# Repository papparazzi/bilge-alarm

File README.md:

# Bilge alarm - M/Y Lada Panas (NMEA 2000 bilge monitor)

Custom 100 x 100 mm, 2-layer PCB for the M/Y Lada Panas (Princess 366, Singapore). It sits behind the helm MFD, watches three pump-sense inputs and a high-water float, drives a light and a buzzer, and reports on an isolated NMEA 2000 (CAN) connection. **Status (11 November 2026): the Rev C.5 boards are built and board 1 works as designed on the bench. Power, all four inputs, the sensor, Wi-Fi and the web page are tested, and the alarm firmware (1.0.0-rc1) runs on it. Still to test, on the boat: the light and buzzer outputs with real loads, and NMEA 2000 on a live network.** Details under [Test status and known risks](#test-status-and-known-risks).

Board 1 running the alarm firmware from 12 V, in the printed enclosure base.

## 3D-printed enclosure

A two-part case (base + removable cover, M3 heat-set inserts, cable strain relief, tie-down lugs) designed to sit behind the helm display. The picture shows the base with the real board (KiCad 10 STEP export with silkscreen) and the ESP32 dev board fitted, cover off. Print files, the parametric Fusion script and rebuild instructions are in [`case/`](case/README.md). **Printed in November 2026; the photo at the top shows the real board in the printed base.**

## Gallery
**The real thing** (November 2026): the dev-board sockets with their pin labels, and the ESP32-S3 dev board that plugs into them.

**The board** (Rev C.5, KiCad 10 ray-traced renders of the real design file):

**The enclosure** (Fusion renders; the board and the ESP32 dev board are the real models/photo):

## What it does
- **Brain:** ESP32-S3-DevKitC-1 clone (N8R2/N16R8) on two 1x22 sockets. The ESP32 module is not assembled by JLCPCB's Economic service, so the dev board is bought separately and plugged in.
- **Power:** 12 V boat battery in, reverse-polarity P-FET, 24.4 V TVS, 2 A PPTC, AP63205 5 V buck feeding the dev-board 5V pin through a Schottky (the dev board makes 3.3 V).
- **Inputs:** three pump-sense inputs and a high-water float (100k/27k dividers, ADC), supply-voltage sense, MUTE button.
- **Outputs:** light and buzzer switched on the **positive** (high-side AO3401A P-FETs, driven by AO3400A), flyback diodes, and a **hard-wired bypass** so the float turns both outputs on even if the ESP32 is dead.
- **NMEA 2000:** CA-IS3050G isolated CAN transceiver (5 kVrms), 8.85 mm copper gap, bus-side L78L05 supply.
- **Sensor:** TE MS5637-02BA03 pressure + temperature on I2C 0x76 (compartment temperature; no humidity).
- **Indicators:** two red LEDs (status, alarm), widely spaced.
- **Extras:** all unused dev-board pins plus 3V3 / 5V / GND and SDA/SCL are broken out on numbered pad rows for solder-on sensors; four M3 corner holes for a 3D-printed case; the Lada Panas logo (32 mm) on the silkscreen.

## Firmware
The alarm firmware is in [`firmware/bilge_alarm`](firmware/bilge_alarm/README.md) (version 1.0.0-rc1, Arduino core for ESP32, built with arduino-cli or the Arduino IDE). It runs on board 1.

- **Alarms:** high water (float), pump running too long, pump starting too often, supply voltage low. Limits are set on the web page.
- **Counts since power-on:** how often and how long each input was on, how often each alarm was raised, and a log of the last 80 events. They survive a restart and a firmware update.
- **Web page** on the boat's Wi-Fi, with every reading the board has. If the board cannot join its saved network it opens its own setup hotspot, where a network can be chosen. Firmware updates are uploaded from the same page.
- **NMEA 2000:** pump and float states, supply voltage, pressure, temperature, and alarms as alert messages for a chartplotter (written for a Raymarine Axiom). Not yet tried on a network.
- **Bluetooth:** advertises as a RuuviTag temperature and pressure sensor for a Victron Cerbo GX. Not yet tried against a Cerbo.

The page as served by board 1 on the bench, in setup-hotspot mode. Nothing is connected to the NMEA 2000 port, so that card reads "no other device answers".

## Repository layout
| Folder | Contents |
|---|---|
| `docs/` | Design decisions, dev-board pin map, holistic review, JLCPCB quotes and sensor comparison, bring-up checklist, DRC and verification output |
| `firmware/` | `bilge_alarm/` is the alarm firmware, `bench_test/` the sketch used to check a new board (arduino-cli, ESP32 Arduino core 3.x). Build, flash and bench instructions are in `firmware/README.md`; the research behind the NMEA 2000, Signal K and Victron choices is `docs/FIRMWARE_ARCHITECTURE.md` |
| `kicad/` | KiCad 10 board: `bilge_n2k_revC.kicad_pcb` (placed, unrouted) and `bilge_n2k_revC_routed.kicad_pcb` (final) |
| `gen/` | Python generators: `design_revC.py` is the single source of the netlist and BOM; `build_pcb.py` places the board; `route_clean.sh` autoroutes (Freerouting) until DRC is clean; `verify_board.py`, `fix_silk.py`, `fix_refs.py`, `export_fab.sh`, `make_quote_files.py`, `make_logo.py` do the rest. `fp/` holds the custom MS5637 footprint |
| `case/` | 3D-printed enclosure: STL/STEP in `print/`, parametric Fusion script in `BilgeCase/`, KiCad STEP exports and ESP32 texture in `ref/`, renders, build notes in `case/README.md` |
| `quote_jlcpcb/` | Files uploaded to JLCPCB: Gerbers + drill zip, BOM, CPL (Economic assembly, top side) |
| `mfg/` | Assembly and copper previews, netlist |
| `logo/` | Source logo and the silkscreen preview |
| `datasheets/` | Datasheets, dev-board dimension drawings and the clone photos used for the footprint; see `SOURCES.md` |
| `review/` | Self-contained zip for an independent reviewer |

## Rebuilding
Needs KiCad 10, Java 25 and Freerouting 2.5 (paths are set at the top of `gen/route.sh`), Python 3 with OpenCV for the logo.
```
python3 gen/design_revC.py            # netlist, BOM, cost
kicad-python gen/build_pcb.py         # place the board (KiCad's bundled Python)
gen/route_clean.sh                    # route until DRC is clean
gen/verify_board.py, gen/fix_silk.py, gen/fix_refs.py, gen/export_fab.sh, gen/make_quote_files.py
```
`gen/make_all.sh` shows the original sequence. Scripts assume this folder layout.

## Ordering (JLCPCB)
Economic assembly, top side, 5 boards: **US$92.12** at the last quote (PCB $4.00, assembly $88.12 including an $18.54 extended-component fee), 26 BOM lines. The MS5637 is flagged "difficult to process" by JLCPCB and must be ticked by hand; they may refuse or surcharge it (fallback: leave it unpopulated and hand-solder). Details in `docs/QUOTES_revC.md`.

## Test status and known risks
The board works as designed in everything tested so far. All testing has been on the bench with board 1; nothing has run on the boat yet. Full results are in `docs/BENCH_RESULTS.md`.

| Area | State |
|---|---|
| Power from 12 V (reverse-polarity FET, 5 V buck) | Tested, works |
| Dev board on the sockets: pin order, power pins, flashing over USB | Tested, works |
| Inputs IN1 to IN4 with 12 V applied | Tested, work |
| Supply voltage reading | Tested, works (read 13.15 V on the bench supply) |
| Pressure and temperature sensor (MS5637, custom footprint) | Tested, works |
| Status LED, MUTE button | Tested, work |
| Wi-Fi, setup hotspot, web page, firmware update over Wi-Fi | Tested, work |
| Alarm logic, counters, event log | Tested with the low-voltage alarm and real 12 V on two inputs |
| Light and buzzer outputs | **Pending.** The pins switch, but no load has been connected |
| Hard-wired float bypass, alarm LED | **Pending** |
| NMEA 2000 | **Pending field test.** The firmware sends with no network attached and never holds anything up; the port has not been on a real network |
| Bluetooth to the Cerbo GX | **Pending.** Advertising runs; not tried against a Cerbo |

Risks closed by the bench test:
- The dev-board clone's pin order and its 3V3 / 5V / GND pins were taken from seller photos and a drawing. They are right: the board runs on the sockets and every tested function is on the expected pin.
- The custom MS5637 footprint and JLCPCB's manual-review risk: the sensor was assembled, answers and passes its calibration check.

Risks still open:
- **Outputs.** The high-side light and buzzer stage has never driven a real load, and the hard-wired bypass (float switches both outputs without the ESP32) has not been tried.
- **NMEA 2000.** Untested on a network. The alarm messages (PGN 126983 / 126985) are built by hand and checked only against the canboat database; a Raymarine Axiom needs LightHouse 4 v4.8.164 or later to show them. The heat of the L78L05 on a 14 to 16 V bus has not been measured.
- **Supply reading.** Single readings jump by up to 1 V with Wi-Fi on; the firmware filters them. The reading may stop rising at about 14.1 V, to be confirmed with an adjustable supply.
- **IN1 and IN2 share their converter (ADC2) with Wi-Fi.** No failed reading so far (about 2.5 million each over a nine-hour run, in hotspot mode and on a normal network); the firmware counts failures and shows them. A next board revision should move them to ADC1.
- **One unexplained restart.** The board once reported a brownout as its last restart cause on the bench. It may only have been the moment 12 V was switched on.
- **USB and 12 V connected at the same time** has not been tested.
- **By design:** while the float is up, the hardware holds light and buzzer on and MUTE cannot silence them.
- **Network access is basic.** Anyone on the same network can read the page; changes ask for a login only once an admin password is set.
- The autorouted layout has not been reviewed by a human (buck loop, CAN pair), and nothing has been measured for emissions.
- Only board 1 has been powered, and only on the bench: no heat, vibration or damp-air exposure yet.

Earlier design notes: `docs/HOLISTIC_REVIEW_revC3.md` and `docs/BRINGUP_CHECKLIST.md`.

## Revision history (short)
Rev C.1-C.3: JLCPCB-only, high-side outputs, MS5637, 100 x 100 mm, I/O on one edge. Rev C.4: re-layout for the clone's real 25.40 mm row spacing. Rev C.5: external-review fixes (22 uF buck output caps, 22k gate pull-ups so |Vgs| stays under 12 V, 470 ohm LED resistors, 2 A PPTC), full silkscreen cleanup, Lada Panas logo.

Datasheets and vendor drawings in `datasheets/` belong to their manufacturers and are included for reference only.

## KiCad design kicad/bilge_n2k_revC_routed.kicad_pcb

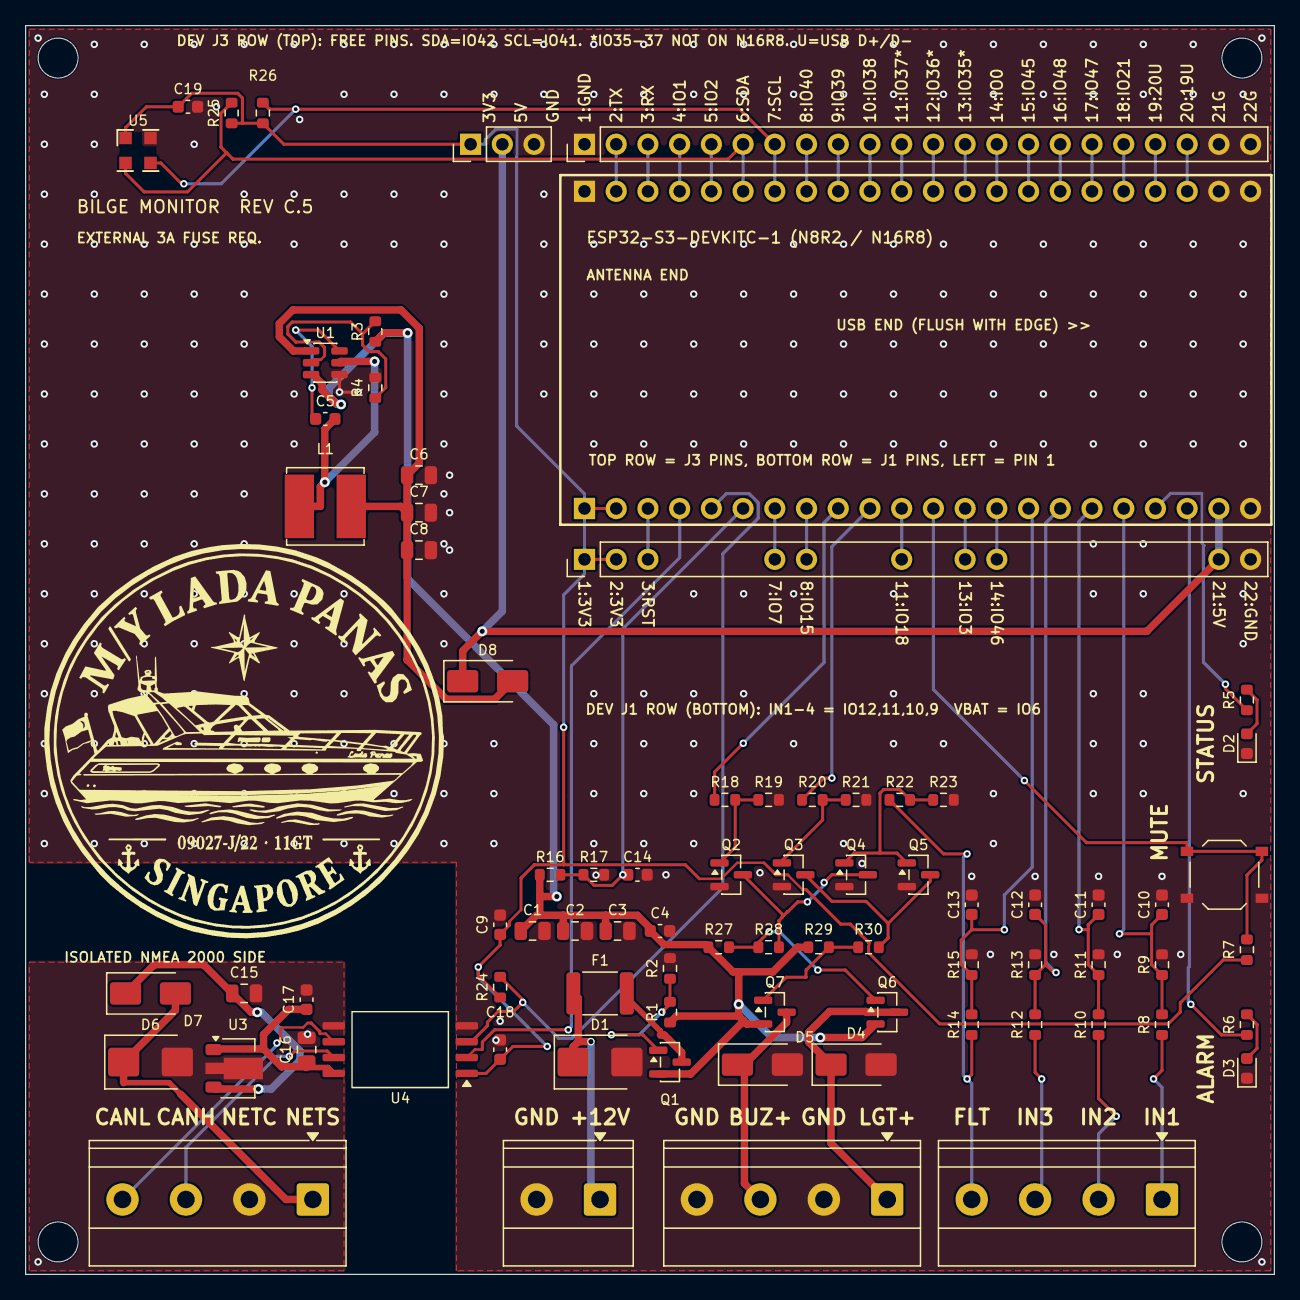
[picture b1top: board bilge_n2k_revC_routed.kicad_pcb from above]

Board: 2 copper layers, 100.0 x 100.0 mm, 84 parts (0 on the bottom side), 69 nets.

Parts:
BR1, BR2: M3; PinHeader_1x22_P2.54mm_Vertical
C1, C2, C3, C15, C16: CL21A106KAYNNNE; C_0805_2012Metric
C4, C5, C9, C10, C11, C12, C13, C14, C17, C18, C19: CC0603KRX7R9BB104; C_0603_1608Metric
C6, C7, C8: CL21A226MAQNNNE; C_0805_2012Metric
D1, D6: SMBJ15CA; D_SMB
D2, D3: KT-0603R; LED_0603_1608Metric
D4, D5, D7, D8: SS14; D_SMA
F1: SMD1812-200-24; Fuse_1812_4532Metric
H1, H2, H3, H4: M3; MountingHole_3.2mm_M3
HDR1, HDR2: HC-PM254-8.5H-1x22PZ; PinSocket_1x22_P2.54mm_Vertical
J1: DB127S-5.08-2P-GN-S; TerminalBlock_Phoenix_MKDS-1,5-2-5.08_1x02_P5.08mm_Horizont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
J2, J3, J4: DB127S-5.08-4P-GN-S; TerminalBlock_Phoenix_MKDS-1,5-4-5.08_1x04_P5.08mm_Horizont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
L1: SRN6045TA-4R7M; L_Bourns_SRN6045TA
PW1: M3; PinHeader_1x03_P2.54mm_Vertical
Q1, Q6, Q7: AO3401A; SOT-23
Q2, Q3, Q4, Q5: AO3400A; SOT-23
R1, R4, R23, R28, R30: 0603WAF4702T5E; R_0603_1608Metric
R2, R3, R8, R10, R12, R14, R16, R19, R21, R22: 0603WAF1003T5E; R_0603_1608Metric
R5, R6: 0603WAF4700T5E; R_0603_1608Metric
R7, R24: 0603WAF1002T5E; R_0603_1608Metric
R9, R11, R13, R15, R17: 0603WAF2702T5E; R_0603_1608Metric
R18, R20: 0603WAF1001T5E; R_0603_1608Metric
R25, R26: 0603WAF5101T5E; R_0603_1608Metric
R27, R29: 0603WAF2202T5E; R_0603_1608Metric
SW3: TS-1187A-B-A-B; SW_Push_1P1T_XKB_TS-1187A
U1: AP63205WU-7; TSOT-23-6
U3: L78L05ABUTR; SOT-89-3
U4: CA-IS3050G; SOIC-8_7.5x5.85mm_P1.27mm
U5: MS563702BA03-50; MS5637-02BA03_QFN-4_3x3mm

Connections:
+3V3: BR1.1, BR1.2, C9.1, C18.1, C19.1, HDR1.1, HDR1.2, PW1.1, R7.1, R24.1, R25.1, R26.1, U4.1, U5.1
+5V: C6.1, C7.1, C8.1, D8.2, L1.2, U1.1
+5V_ISO: C16.1, C17.1, U3.1, U4.8
BST: C5.1, U1.6
BTN_MUTE: HDR1.12, R7.2, SW3.1
BUZZ_CTL: HDR1.10, R20.1
BUZZ_OUT: D5.1, J3.3, Q7.3
B_G: Q3.1, R20.2, R21.1
B_PD: Q3.3, Q5.3, R30.2
B_PG: Q7.1, R29.2, R30.1
CANH_J: J4.3, U4.7
CANL_J: J4.4, U4.6
CAN_RX: HDR1.4, U4.2
CAN_TX: HDR1.5, R24.2, U4.3
DEV_5V: BR1.21, D8.1, HDR1.21, PW1.2
EN_BUCK: R3.2, R4.1, U1.2
GND: BR1.22, BR2.1, BR2.21, BR2.22, C1.2, C2.2, C3.2, C4.2, C6.2, C7.2, C8.2, C9.2, C10.2, C11.2, C12.2, C13.2, C14.2, C18.2, C19.2, D1.2, D2.1, D3.1, D4.2, D5.2, HDR1.22, HDR2.1, HDR2.21, HDR2.22, J1.2, J3.2, J3.4, PW1.3, Q2.2, Q3.2, Q4.2, Q5.2, R2.2, R4.2, R9.2, R11.2, R13.2, R15.2, R17.2, R19.2, R21.2, R23.2, SW3.2, U1.4, U4.4, U5.4
HW_G: Q4.1, Q5.1, R22.2, R23.1
I2C_SCL: BR2.7, HDR2.7, R26.2, U5.3
I2C_SDA: BR2.6, HDR2.6, R25.2, U5.2
IN1_A: C10.1, HDR1.18, R8.2, R9.1
IN1_RAW: J2.1, R8.1
IN2_A: C11.1, HDR1.17, R10.2, R11.1
IN2_RAW: J2.2, R10.1
IN3_A: C12.1, HDR1.16, R12.2, R13.1
IN3_RAW: J2.3, R12.1
IN4_A: C13.1, HDR1.15, R14.2, R15.1
IN4_RAW: J2.4, R14.1, R22.1
J1_P3: BR1.3, HDR1.3
J1_P7: BR1.7, HDR1.7
J1_P8: BR1.8, HDR1.8
J1_P11: BR1.11, HDR1.11
J1_P13: BR1.13, HDR1.13
J1_P14: BR1.14, HDR1.14
J3_P2: BR2.2, HDR2.2
J3_P3: BR2.3, HDR2.3
J3_P4: BR2.4, HDR2.4
J3_P5: BR2.5, HDR2.5
J3_P8: BR2.8, HDR2.8
J3_P9: BR2.9, HDR2.9
J3_P10: BR2.10, HDR2.10
J3_P11: BR2.11, HDR2.11
J3_P12: BR2.12, HDR2.12
J3_P13: BR2.13, HDR2.13
J3_P14: BR2.14, HDR2.14
J3_P15: BR2.15, HDR2.15
J3_P16: BR2.16, HDR2.16
J3_P17: BR2.17, HDR2.17
J3_P18: BR2.18, HDR2.18
J3_P19: BR2.19, HDR2.19
J3_P20: BR2.20, HDR2.20
LED_ALM: HDR1.20, R6.1
LED_ALM_A: D3.2, R6.2
LED_STAT: HDR1.19, R5.1
LED_STAT_A: D2.2, R5.2
LIGHT_CTL: HDR1.9, R18.1
LIGHT_OUT: D4.1, J3.1, Q6.3
L_G: Q2.1, R18.2, R19.1
L_PD: Q2.3, Q4.3, R28.2
L_PG: Q6.1, R27.2, R28.1
NET_C: C15.2, C16.2, C17.2, D6.2, J4.2, U3.2, U4.5
NET_S: D6.1, D7.2, J4.1
NET_SP: C15.1, D7.1, U3.3
Q1_G: Q1.1, R1.2, R2.1
SW: C5.2, L1.1, U1.5
VBAT_IN: D1.1, F1.1, J1.1
VFUSED: F1.2, Q1.3
VIN: C1.1, C2.1, C3.1, C4.1, Q1.2, Q6.2, Q7.2, R1.1, R3.1, R16.1, R27.1, R29.1, U1.3
VSENSE_A: C14.1, HDR1.6, R16.2, R17.1

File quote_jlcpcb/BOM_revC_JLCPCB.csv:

Comment,Designator,Footprint,LCSC Part #
10 uF 25 V X5R 0805,"C1,C2,C3,C15,C16",C0805,C15850
100 nF 50 V X7R 0603 (JLCPCB Basic),"C4,C5,C9,C10,C11,C12,C13,C14,C17,C18,C19",C0603,C14663
22 uF 25 V X5R 0805 (JLCPCB Basic; buck COUT per AP63205 DS41326),"C6,C7,C8",C0805,C45783
"TVS 600 W bidirectional, VRWM 15 V, VBR 16.7-18.5 V, VC 24.4 V","D1,D6",DO-214AA (SMB),C19077570
LED red 0603,"D2,D3",LED0603,C2286
Schottky 40 V 1 A,"D4,D5,D7,D8",DO-214AC (SMA),C2480
"PPTC 2 A hold, 4 A trip, 24 V",F1,1812,C46641174
"1x22 female header 2.54 mm, 8.5 mm tall (dev-board socket)","HDR1,HDR2",THT 2.54 mm 1x22,C41376161
"Screw terminal 5.08 mm, 2 pos, side entry",J1,THT 5.08 mm,C2997519
"Screw terminal 5.08 mm, 4 pos, side entry","J2,J3,J4",THT 5.08 mm,C2997521
"4.7 uH 20 %, shielded, 6x6 mm (4.7 uH = AP63205 datasheet Table 3 for 5 V out)",L1,SMD 6x6 mm,C2044594
"P-MOSFET -30 V -4 A, VGS +-12 V","Q1,Q6,Q7",SOT-23,C15127
"N-MOSFET 30 V 5.7 A, VGS +-12 V, logic level","Q2,Q3,Q4,Q5",SOT-23,C20917
47 k 1 % 0603,"R1,R4,R23,R28,R30",R0603,C25819
100 k 1 % 0603,"R2,R3,R8,R10,R12,R14,R16,R19,R21,R22",R0603,C25803
470 ohm 1 % 0603,"R5,R6",R0603,C23179
10 k 1 % 0603,"R7,R24",R0603,C25804
27 k 1 % 0603,"R9,R11,R13,R15,R17",R0603,C22967
1 k 1 % 0603,"R18,R20",R0603,C21190
5.1 k 1 % 0603,"R25,R26",R0603,C23186
22 k 1 % 0603,"R27,R29",R0603,C31850
Tactile switch 5.1x5.1 mm SMD,SW3,SMD 5.1x5.1,C318884
"5 V 2 A buck, 3.8-32 V in, TSOT-26",U1,TSOT-23-6,C2071056
"5 V 100 mA linear regulator, 30 V in",U3,SOT-89-3,C42738
"5 kVrms isolated CAN transceiver, VCC1 2.5-5.5 V, VCC2 4.5-5.5 V",U4,SOIC-8 wide (7.5 mm body),C528763
"Barometric pressure + temperature sensor, I2C 0x76, 300-1200 mbar",U5,QFN-4 (3x3),C3033010

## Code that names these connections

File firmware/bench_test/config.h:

// Bilge alarm Rev C.5 - bench test firmware: pins and constants.
// Pin map source: docs/DEVBOARD_PINMAP_revC.md (ESP32-S3-DevKitC-1 clone on sockets).
#pragma once

#define FW_NAME    "bilge-alarm bench test"
#define FW_VERSION "0.1.0"

// ---- GPIO (dev board J1 row unless noted)
#define PIN_CAN_RX    4    // CA-IS3050G RXD
#define PIN_CAN_TX    5    // CA-IS3050G TXD (10k pull-up on the PCB)
#define PIN_VSENSE    6    // ADC1: supply voltage, 100k/27k
#define PIN_BTN_MUTE  8    // active low, 10k pull-up on the PCB
#define PIN_IN4       9    // ADC1: high-water float
#define PIN_IN3       10   // ADC1: pump 3 run
#define PIN_IN2       11   // ADC2: pump 2 run (ADC2 shares hardware with Wi-Fi)
#define PIN_IN1       12   // ADC2: pump 1 run (ADC2 shares hardware with Wi-Fi)
#define PIN_LED_STAT  13   // active high, 470R
#define PIN_LED_ALM   14   // active high, 470R
#define PIN_LIGHT     16   // active high -> Q2 -> high-side Q6 -> LGT+
#define PIN_BUZZ      17   // active high -> Q3 -> high-side Q7 -> BUZ+
#define PIN_I2C_SCL   41   // dev board J3 row
#define PIN_I2C_SDA   42   // dev board J3 row

// ---- analogue front end: 100k (top) / 27k (bottom) on IN1-4 and VSENSE
#define DIVIDER_RATIO (127.0f / 27.0f)
#define IN_ON_VOLTS   8.0f   // input counts as active at or above this
#define IN_OFF_VOLTS  6.0f   // and as inactive again below this

// ---- NMEA 2000
#define CAN_BITRATE_KBPS 250

// ---- Wi-Fi
#define HOSTNAME               "bilge-alarm"   // http://bilge-alarm.local
#define AP_SSID_PREFIX         "BilgeAlarm-"   // + last 4 hex digits of the MAC
#include "secrets.h"                           // AP_PASSWORD, the setup hotspot password. Missing? Copy secrets.example.h to secrets.h
#define STA_CONNECT_TIMEOUT_MS 20000UL         // no connection after this: start the setup hotspot
#define STA_LOST_REBOOT_MS     60000UL         // connection lost for this long: reboot (then hotspot if it still fails)
#define AP_RETRY_STA_MS        300000UL        // hotspot idle this long with a saved network: reboot and try it again

// ---- MUTE button
#define MUTE_LONG_PRESS_MS 1500UL   // hold = lamp and buzzer test

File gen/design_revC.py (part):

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P("D1", "SMBJ15CA", "SMB", {"1": "VBAT_IN", "2": "GND"}, "supply TVS, bidirectional", B)
P("F1", "SMD1812-200-24", "PPTC", {"1": "VBAT_IN", "2": "VFUSED"}, "board PPTC 2 A hold, 4 A trip (1.5 A hold derated too far at 50 C behind the MFD)", B)
# reverse polarity: P-FET, drain = input side, source = protected rail; gate divider keeps |VGS| = 0.32 x VIN
P("Q1", "AO3401A", "SOT23", {"1": "Q1_G", "2": "VIN", "3": "VFUSED"}, "reverse-polarity P-FET (pin 1 G, 2 S, 3 D)", B)
R("47k", "VIN", "Q1_G", "Q1 gate divider top", B)
R("100k", "Q1_G", "GND", "Q1 gate divider bottom", B)
for _ in range(3):
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for _ in range(3):
    C("22u", "+5V", "GND", "buck COUT (22 uF per AP63205 datasheet)", B)
# series Schottky: our 5 V can feed the dev board but USB 5 V can never back-feed the buck
P("D8", "SS14", "SMA", {"1": "DEV_5V", "2": "+5V"}, "+5V -> dev-board 5V pin (cathode = DEV_5V); blocks back-feed from the dev-board USB port", B)

# ================================================================ DEV BOARD (ESP32-S3-DevKitC-1 pattern, 2 x 22 pins; clone: rows 25.40 mm apart, see DEVBOARD_PINMAP_revC.md)
B = "MCU"
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P("HDR2", "HC-PM254-8.5H-1x22PZ", "SOCK", hdr2, "dev board J3: 1 G | 2 TX | 3 RX | 4 GPIO1 | 5 GPIO2 | 6-13 GPIO42,41,40,39,38,37,36,35 | 14 GPIO0 | 15 GPIO45 | 16 GPIO48 | 17 GPIO47 | 18 GPIO21 | 19 GPIO20 | 20 GPIO19 | 21,22 G", B)
C("100n", "+3V3", "GND", "3V3 decoupling for U4 side", B)
R("470", "LED_STAT", "LED_STAT_A", "LED series (about 3 mA)", B)
P("D2", "KT-0603R", "LED", {"1": "GND", "2": "LED_STAT_A"}, "status LED red (cathode pin 1); same part as D3 so it is JLCPCB Basic", B)
R("470", "LED_ALM", "LED_ALM_A", "LED series (about 3 mA)", B)
P("D3", "KT-0603R", "LED", {"1": "GND", "2": "LED_ALM_A"}, "alarm LED red (cathode pin 1)", B)
R("10k", "+3V3", "BTN_MUTE", "MUTE pull-up", B)
P("SW3", "TS-1187A-B-A-B", "SW", {"1": "BTN_MUTE", "2": "GND"}, "MUTE (long press = lamp/buzzer test); RESET and BOOT are the dev board's own buttons", B)

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
# ================================================================ MS5637 barometric pressure + temperature (I2C, address 0x76; TE datasheet 06/2017 p.14)
B = "Sensor"
P("U5", "MS563702BA03-50", "MS5637", {"1": "+3V3", "2": "I2C_SDA", "3": "I2C_SCL", "4": "GND"}, "pin 1 VDD, 2 SDA, 3 SCL, 4 GND (pads seen from above: pin 1 top-left, 2 bottom-left, 3 bottom-right, 4 top-right)", B)
R("5.1k", "+3V3", "I2C_SDA", "I2C pull-up", B)
R("5.1k", "+3V3", "I2C_SCL", "I2C pull-up", B)
C("100n", "+3V3", "GND", "MS5637 VDD bypass (datasheet: 100 nF at the VDD pin)", B)
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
